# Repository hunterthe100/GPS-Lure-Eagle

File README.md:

# GPS-Lure 
A lure for the MinnowBoard Max & MinnowBoard Turbot.  Copyright (C) 2015 Smallworks, LLC

This design is made with [EAGLE CAD](http://www.cadsoftusa.com/eagle-pcb-design-software/about-eagle/) 

Comercially avaliable at: https://store.netgate.com/Lures/GPS.aspx

This work is licensed under a Creative Commons Attribution-ShareAlike 4.0 International License
[  
*Licensing CC BY-SA 4.0*](http://creativecommons.org/licenses/by-sa/4.0/)

It may be used for Educational, Personal, or Commercial Use, provided you keep these notices,
attribution, and share-alike. When you apply these licenses to material you create, 
it meets the Freedom Defined definition of a "Free Cultural Work". 
Free cultural works are the ones that can be most readily used, shared, 
and remixed by others, and go furthest toward creating a commons of freely reusable materials.

-------------------------------------------------------------------------------------------

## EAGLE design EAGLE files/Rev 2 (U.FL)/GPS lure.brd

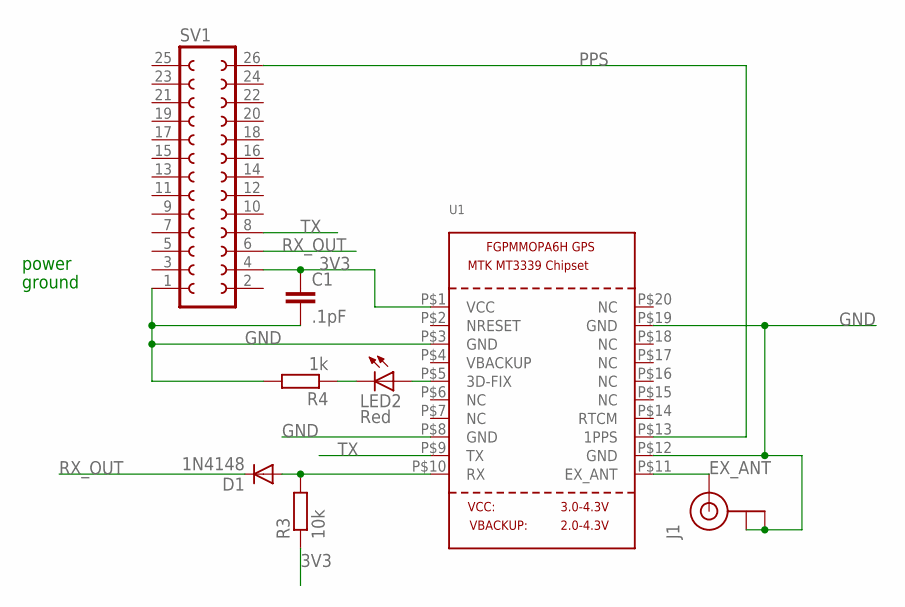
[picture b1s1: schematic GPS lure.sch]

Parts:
C1: .1pF; C0805
D1: 1N4148; SOD123
J1: U.FL
LED2: Red; CHIPLED_1206
R3: 10k; M1206
R4: 1k; M1206
SV1: FE13-2
U1: GPS_FGPMMOPA6H; FGPMMOPA6H

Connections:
3V3: C1.1, R3.1, SV1.4, U1.P$1 (VCC)
EX_ANT: J1.P$3 (SIGNAL), U1.P$11 (EX_ANT)
GND: C1.2, J1.P$1 (GND), J1.P$2 (GND), R4.2, SV1.1, U1.P$3 (GND), U1.P$8 (GND), U1.P$12 (GND), U1.P$19 (GND)
unnamed: LED2.A, U1.P$5 (3D-FIX)
unnamed: LED2.C, R4.1
unnamed: D1.A, R3.2, U1.P$10 (RX)
PPS: SV1.26, U1.P$13 (1PPS)
RX_OUT: D1.C, SV1.6
TX: SV1.8, U1.P$9 (TX)

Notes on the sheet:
power
ground

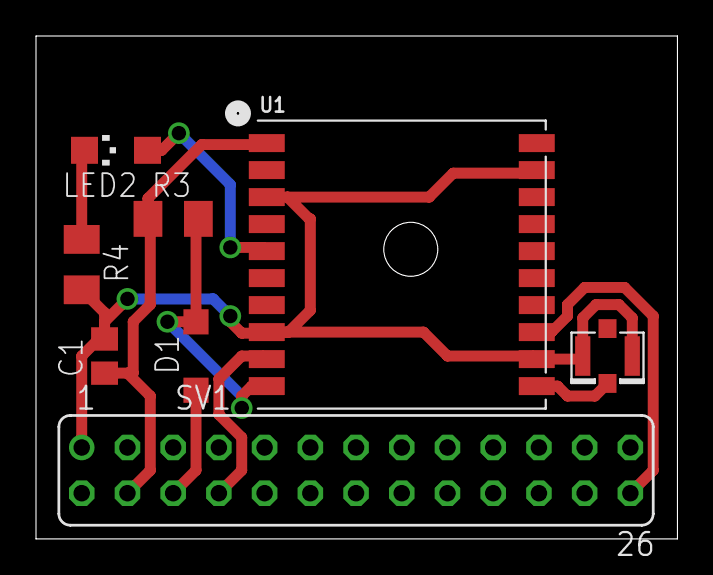
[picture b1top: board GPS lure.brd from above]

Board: 2 copper layers, 35.6 x 27.9 mm, 8 parts (0 on the bottom side), 9 nets.

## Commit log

2016-07-07 Initial Commit
    GPS lure EAGLE files
2016-07-26 New Update / moving of files & renaming
2016-08-08 Updated Eagle Files to make silkscreen cleaner

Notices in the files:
parts and their libraries:
SparkFun-Connectors: Licensing: Creative Commons ShareAlike 4.0 International - https://creativecommons.org/licenses/by-sa/4.0
